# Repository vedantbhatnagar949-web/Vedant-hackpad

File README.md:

# Vedant-hackpad
My custom macropad for easy multimedia access

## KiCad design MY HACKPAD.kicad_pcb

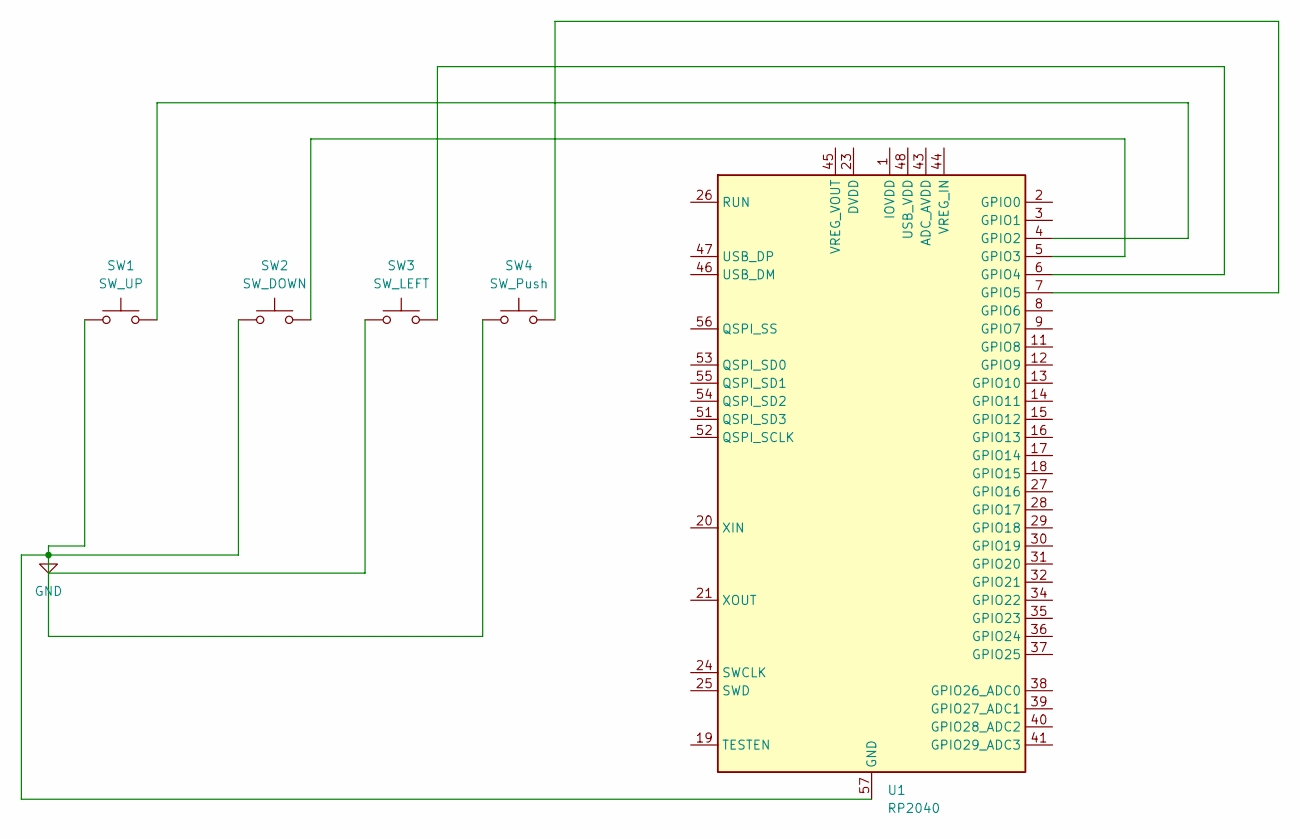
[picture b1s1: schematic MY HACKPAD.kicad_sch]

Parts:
SW1: SW_UP; SW_Cherry_MX_1.00u_PCB
SW2: SW_DOWN; SW_Cherry_MX_1.00u_PCB
SW3: SW_LEFT; SW_Cherry_MX_1.00u_PCB
SW4: SW_Push; SW_Cherry_MX_1.00u_PCB
U1: RP2040; QFN-56-1EP_7x7mm_P0.4mm_EP3.2x3.2mm

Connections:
GND: SW1.1, SW2.1, SW4.1, U1.57 (GND)
unnamed: U1.23 (DVDD), U1.50 (DVDD)
unnamed: SW1.2, U1.4 (GPIO2)
unnamed: SW2.2, U1.5 (GPIO3)
unnamed: SW3.2, U1.6 (GPIO4)
unnamed: SW4.2, U1.7 (GPIO5)
unnamed: U1.1 (IOVDD), U1.10 (IOVDD), U1.22 (IOVDD), U1.33 (IOVDD), U1.42 (IOVDD), U1.49 (IOVDD)

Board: 2 copper layers, 5 parts (0 on the bottom side), 7 nets, no tracks yet.

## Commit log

2025-11-30 the front and back of the case
2025-11-30 Add files via upload
    my hackpads schematic,pcb and pro file
